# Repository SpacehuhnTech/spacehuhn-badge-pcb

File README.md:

# spacehuhn-badge-pcb
The Spacehuhn badge project files

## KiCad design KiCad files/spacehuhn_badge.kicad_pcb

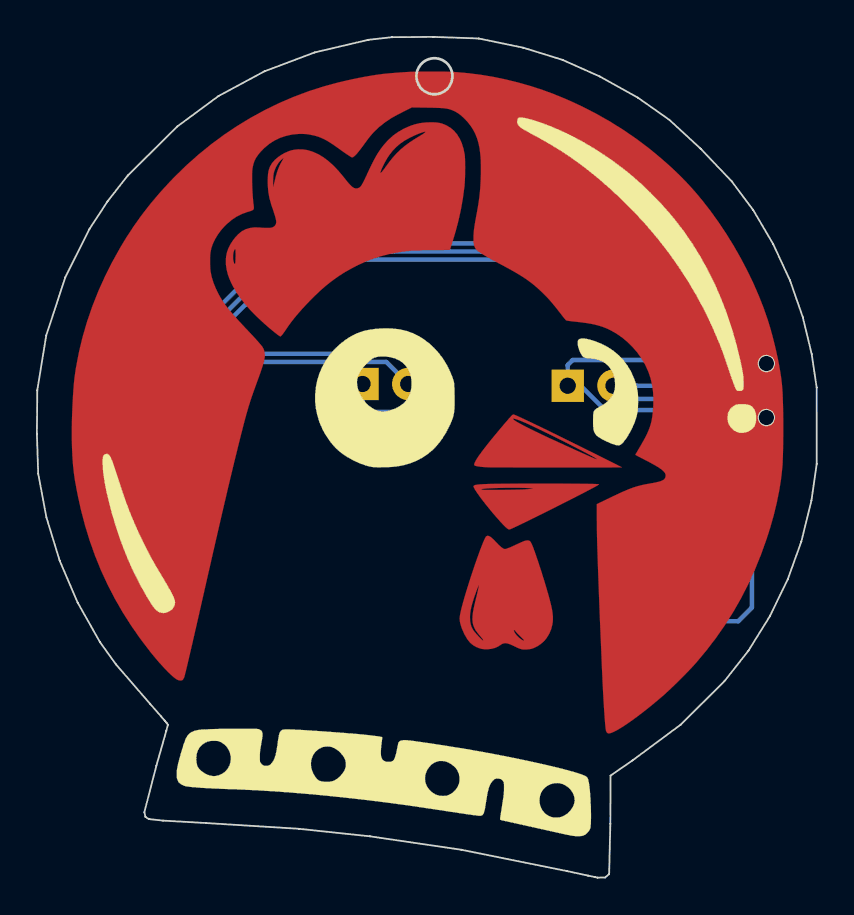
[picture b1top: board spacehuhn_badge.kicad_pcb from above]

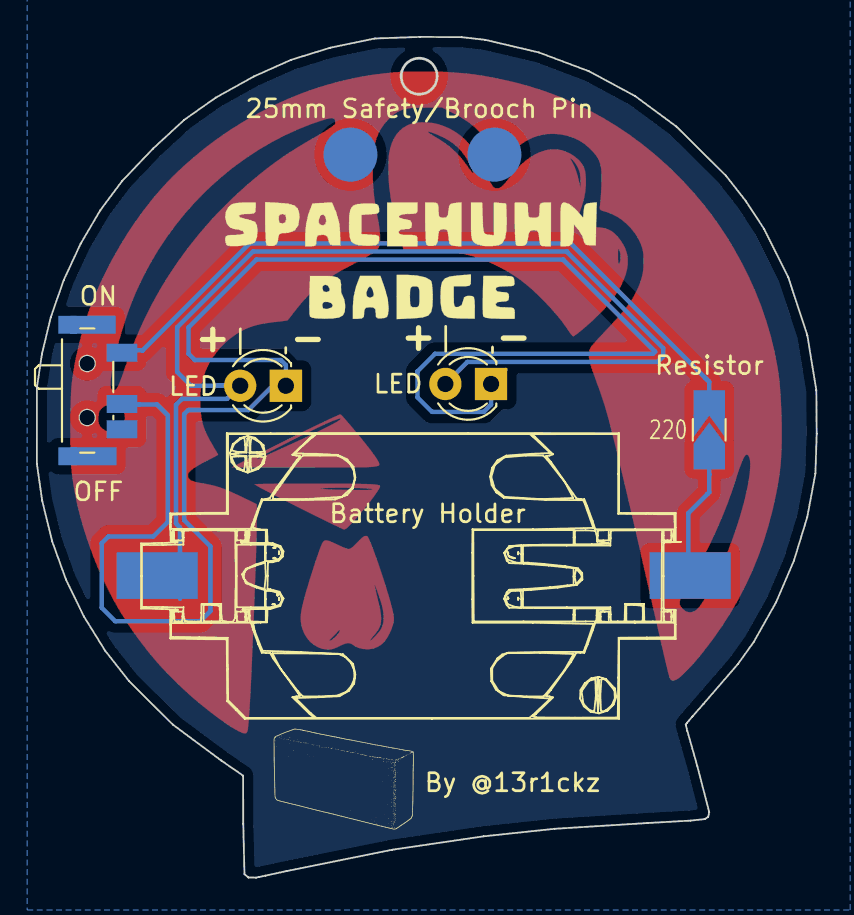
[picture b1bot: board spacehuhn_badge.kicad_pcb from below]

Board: 2 copper layers, 43.3 x 46.7 mm, 6 parts (6 on the bottom side), 4 nets.

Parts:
25mm Safety/Brooch Pin: Brooch_12x5mm
Battery Holder: Battery_Cell; CR2032_Coin_Cell_Holder_WHITE
LED: LED; LED_D3.0mm
LED#2: LED; LED_D3.0mm
ON: SW_DIP_x01; SW_SPDT_PCM12
Resistor: 220; R_1206_3216Metric_Pad1.42x1.75mm_HandSolder

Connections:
+3V0: Battery Holder.1, LED.2, LED#2.2
GND: LED.1, LED#2.1, ON.2
unnamed: Battery Holder.2, Resistor.1
unnamed: ON.1, Resistor.2

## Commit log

2020-11-27 File release
2020-11-27 add premade Gerber Zip
